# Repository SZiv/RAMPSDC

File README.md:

# RAMPSDC
RAMPS Due Converter. 
See the Wiki here: http://reprap.org/wiki/RAMPSDC (still working on it)

Goes between a standard 5V RAMPS, and a 3.3V Arduino Due. Uses the Vin from the RAMPS board to power the 5V rail, and then uses that 5V supply to power pins on the RAMPS, allowing more current for the Heater and Servo pins outputs. 
Steps down voltage of the X Max, Y max, Y min, Xmin, and Z min endstops (The Z MAX Enstop is unconnected), so they dont damage the Due, and a 5V-3.3V voltage divider is used to propotionally drop the voltage of the Thermistors.
Also adds the EEPROM required for use as a 3D printer controller.

Uses three generic bidirectional level shifter modules (two if you arn't using servos). These can be bought from Ebay or Aliexpress for maybe 50 cents each. Just make sure you get the kind with the powers and grounds (HV, GND, LV, GND) in the middle. Other than that, its a pretty generic part.

Most other pins are connected to the RAMPS as if it was a mega (Digital pin 51 > digital pin 51, RX > RX, TX > TX, ETC). It is worth noting that since the pins dont perfectly match up, I2C 1 (which is normally broken out on the RAMPS), is used by the EEPROM, so the 2nd I2C header is broken out on the RAMPS. The SPI pins are not in the same place as the mega, and are broken out behind the RAMPS connector.

As a reminder, all inputs, INCLUDING the Analog inputs, MUST be reduced to 3.3V before hitting the due. This means you cannot use an LCD screen with this, without some sort of voltage regulation on the encoder. I'm still working on a workaround for this, and that may show up in V2.

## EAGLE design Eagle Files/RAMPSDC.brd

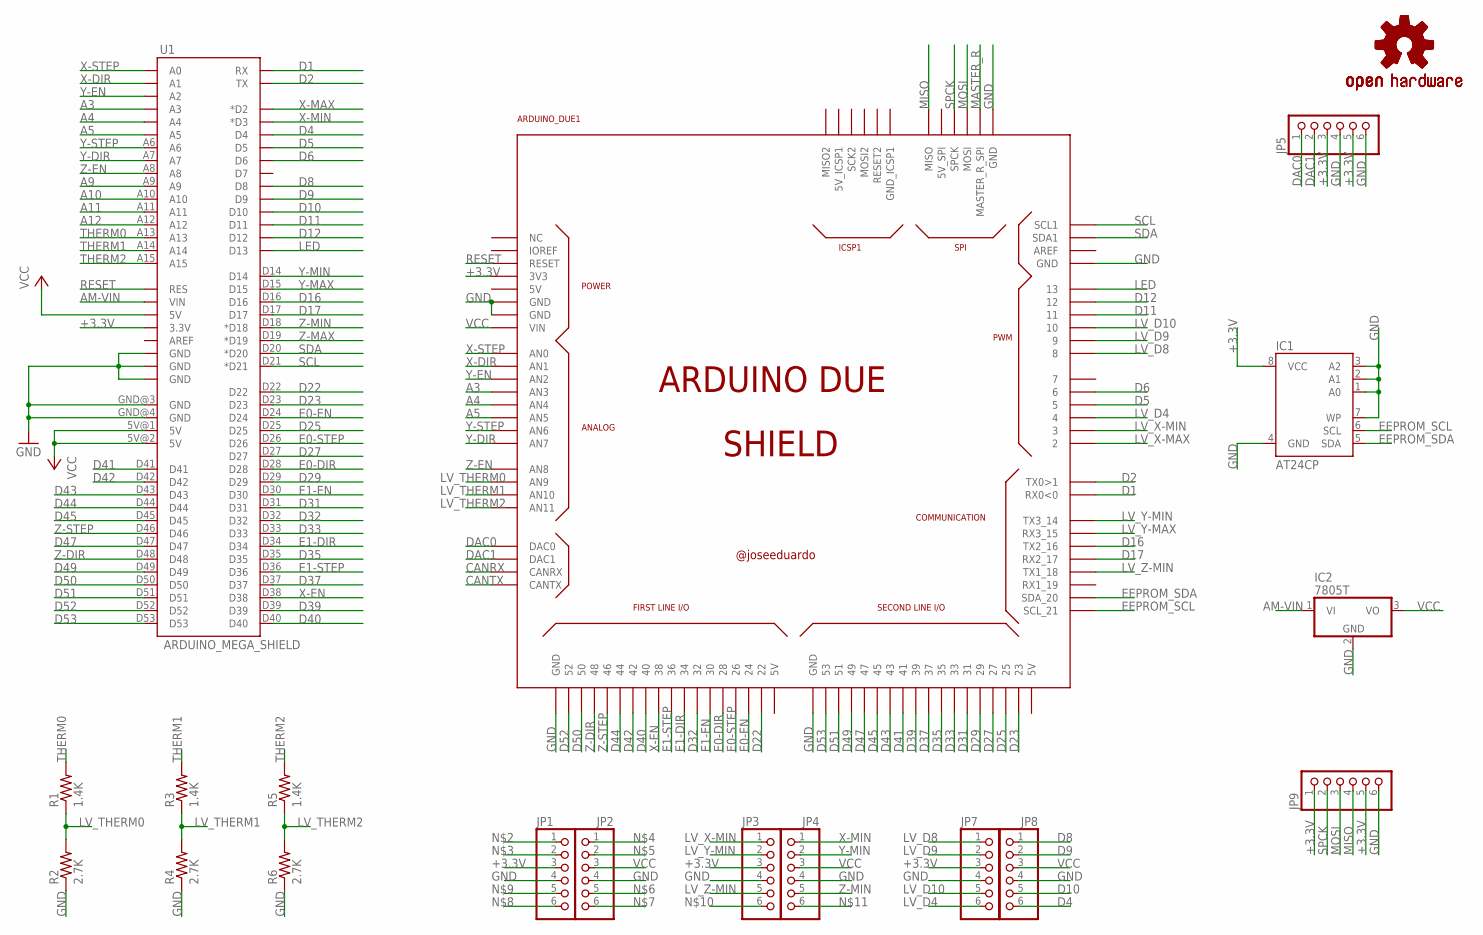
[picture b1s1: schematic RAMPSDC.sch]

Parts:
ARDUINO_DUE1: ARDUINO_DUE_SHIELD
IC1: AT24CP; DIL08
IC2: 7805T; TO220H
JP1, JP2, JP3, JP4, JP5, JP7, JP8, JP9: PINHD-1X6; 1X06
LOGO1: OSHW-LOGOS; OSHW-LOGO-S
LOGO2: OSHW-LOGOL-COPPER; OSHW-LOGO-L_COPPER
R1, R3, R5: 1.4K; R0805
R2, R4, R6: 2.7K; R0805
U1: ARDUINO_MEGA_SHIELD

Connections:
+3.3V: ARDUINO_DUE1.3V3, IC1.8 (VCC), JP1.3, JP3.3, JP5.3, JP5.5, JP7.3, JP9.1, JP9.5, U1.3.3V
A3: ARDUINO_DUE1.A3 (AN3), U1.A3
A4: ARDUINO_DUE1.A4 (AN4), U1.A4
A5: ARDUINO_DUE1.A5 (AN5), U1.A5
A9: U1.A9
A10: U1.A10
A11: U1.A11
A12: U1.A12
AM-VIN: IC2.1 (VI), U1.VIN
CANRX: ARDUINO_DUE1.CANRX
CANTX: ARDUINO_DUE1.CANTX
D1: ARDUINO_DUE1.0 (RX0<0), U1.RX
D2: ARDUINO_DUE1.1 (TX0>1), U1.TX
D4: JP8.6, U1.D4
D5: ARDUINO_DUE1.5, U1.D5
D6: ARDUINO_DUE1.6, U1.D6
D8: JP8.1, U1.D8
D9: JP8.2, U1.D9
D10: JP8.5, U1.D10
D11: ARDUINO_DUE1.11, U1.D11
D12: ARDUINO_DUE1.12, U1.D12
D16: ARDUINO_DUE1.16 (TX2_16), U1.D16
D17: ARDUINO_DUE1.17 (RX2_17), U1.D17
D22: ARDUINO_DUE1.22, U1.D22
D23: ARDUINO_DUE1.23, U1.D23
D25: ARDUINO_DUE1.25, U1.D25
D27: ARDUINO_DUE1.27, U1.D27
D29: ARDUINO_DUE1.29, U1.D29
D31: ARDUINO_DUE1.31, U1.D31
D32: ARDUINO_DUE1.32, U1.D32
D33: ARDUINO_DUE1.33, U1.D33
D35: ARDUINO_DUE1.35, U1.D35
D37: ARDUINO_DUE1.37, U1.D37
D39: ARDUINO_DUE1.39, U1.D39
D40: ARDUINO_DUE1.40, U1.D40
D41: ARDUINO_DUE1.41, U1.D41
D42: ARDUINO_DUE1.42, U1.D42
D43: ARDUINO_DUE1.43, U1.D43
D44: ARDUINO_DUE1.44, U1.D44
D45: ARDUINO_DUE1.45, U1.D45
D47: ARDUINO_DUE1.47, U1.D47
D49: ARDUINO_DUE1.49, U1.D49
D50: ARDUINO_DUE1.50, U1.D50
D51: ARDUINO_DUE1.51, U1.D51
D52: ARDUINO_DUE1.52, U1.D52
D53: ARDUINO_DUE1.53, U1.D53
DAC0: ARDUINO_DUE1.DAC0, JP5.1
DAC1: ARDUINO_DUE1.DAC1, JP5.2
E0-DIR: ARDUINO_DUE1.28, U1.D28
E0-EN: ARDUINO_DUE1.24, U1.D24
E0-STEP: ARDUINO_DUE1.26, U1.D26
E1-DIR: ARDUINO_DUE1.34, U1.D34
E1-EN: ARDUINO_DUE1.30, U1.D30
E1-STEP: ARDUINO_DUE1.36, U1.D36
EEPROM_SCL: ARDUINO_DUE1.21 (SCL_21), IC1.6 (SCL)
EEPROM_SDA: ARDUINO_DUE1.20 (SDA_20), IC1.5 (SDA)
GND: ARDUINO_DUE1.GND, ARDUINO_DUE1.GND_1 (GND), ARDUINO_DUE1.GND_2 (GND), ARDUINO_DUE1.GND_3 (GND), ARDUINO_DUE1.GND_4 (GND), ARDUINO_DUE1.GND_5 (GND), IC1.1 (A0), IC1.2 (A1), IC1.3 (A2), IC1.4 (GND), IC1.7 (WP), IC2.2 (GND), JP1.4, JP2.4, JP3.4, JP4.4, JP5.4, JP5.6, JP7.4, JP8.4, JP9.6, R2.1, R4.1, R6.1, U1.GND@0 (GND), U1.GND@1 (GND), U1.GND@2 (GND), U1.GND@3 (GND), U1.GND@4 (GND)
LED: ARDUINO_DUE1.13, U1.D13
LV_D4: ARDUINO_DUE1.4, JP7.6
LV_D8: ARDUINO_DUE1.8, JP7.1
LV_D9: ARDUINO_DUE1.9, JP7.2
LV_D10: ARDUINO_DUE1.10, JP7.5
LV_THERM0: ARDUINO_DUE1.A9 (AN9), R1.1, R2.2
LV_THERM1: ARDUINO_DUE1.A10 (AN10), R3.1, R4.2
LV_THERM2: ARDUINO_DUE1.A11 (AN11), R5.1, R6.2
LV_X-MAX: ARDUINO_DUE1.2
LV_X-MIN: ARDUINO_DUE1.3, JP3.1
LV_Y-MAX: ARDUINO_DUE1.15 (RX3_15)
LV_Y-MIN: ARDUINO_DUE1.14 (TX3_14), JP3.2
LV_Z-MIN: ARDUINO_DUE1.18 (TX1_18), JP3.5
MASTER_R: ARDUINO_DUE1.MASTER_RESET_SPI (MASTER_R_SPI)
MISO: ARDUINO_DUE1.MISO, JP9.4
MOSI: ARDUINO_DUE1.MOSI, JP9.3
RESET: ARDUINO_DUE1.RESET, U1.RES
SCL: ARDUINO_DUE1.SCL1, U1.D21 (*D21)
SDA: ARDUINO_DUE1.SDA1, U1.D20 (*D20)
SPCK: ARDUINO_DUE1.SPCK, JP9.2
THERM0: R1.2, U1.A13
THERM1: R3.2, U1.A14
THERM2: R5.2, U1.A15
VCC: ARDUINO_DUE1.VIN, IC2.3 (VO), JP2.3, JP4.3, JP8.3, U1.5V@0 (5V), U1.5V@1 (5V), U1.5V@2 (5V)
X-DIR: ARDUINO_DUE1.A1 (AN1), U1.A1
X-EN: ARDUINO_DUE1.38, U1.D38
X-MAX: U1.D2 (*D2)
X-MIN: JP4.1, U1.D3 (*D3)
X-STEP: ARDUINO_DUE1.A0 (AN0), U1.A0
Y-DIR: ARDUINO_DUE1.A7 (AN7), U1.A7
Y-EN: ARDUINO_DUE1.A2 (AN2), U1.A2
Y-MAX: U1.D15
Y-MIN: JP4.2, U1.D14
Y-STEP: ARDUINO_DUE1.A6 (AN6), U1.A6
Z-DIR: ARDUINO_DUE1.48, U1.D48
Z-EN: ARDUINO_DUE1.A8 (AN8), U1.A8
Z-MAX: U1.D19 (*D19)
Z-MIN: JP4.5, U1.D18 (*D18)
Z-STEP: ARDUINO_DUE1.46, U1.D46

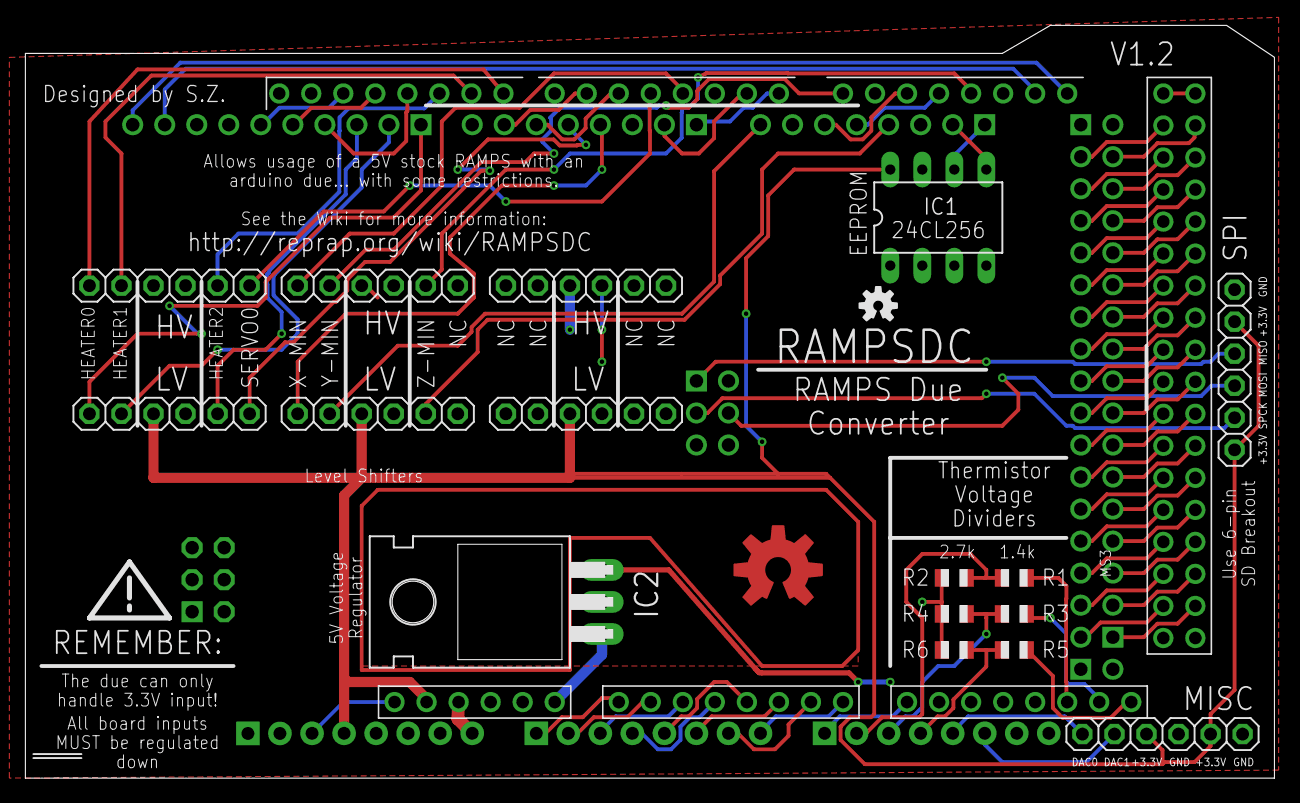
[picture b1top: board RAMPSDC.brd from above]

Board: 2 copper layers, 99.1 x 59.7 mm, 20 parts (0 on the bottom side), 84 nets.

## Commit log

2017-11-18 :tada: Added .gitattributes & .gitignore files
2017-11-18 First Commit! Kachow!
    initial commit
2017-11-18 Update README.md
    typo
2017-11-19 Fixed a critical issue with the Step-downs.
    They are actually seperated by 5 pins, not 6. Derp! Fixed. I'm working
    on a new revision that will get rid of the maximum endstops and servos
    2-4 (disconnect completely), and use that spare driver to regulate an
    LCD screen down, or at least make pinouts for an SD ramps
2017-11-19 Disconnected Max Endstops and Servos 2-4. Added SD card Headers. Fixed some Silkscreen errors.
    This is a step towards making the LCD screen work, but in the meantime,
    the last level shifter was changed to all NC. At some point, that will
    be the encoder button, encoder 1, encoder 2, MISO, and whatever else
    needs to be shifted to make the reprap full graphics controller work.
    The issue is the documentation sucks on that so I need to really dig to
    make it work. In the meantime, I added just a breakout header for the

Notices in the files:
Eagle Files/RAMPSDC.sch:
GPLv3
parts and their libraries:
SparkFun-Aesthetics: Licensing: Creative Commons ShareAlike 4.0 International - https://creativecommons.org/licenses/by-sa/4.0
